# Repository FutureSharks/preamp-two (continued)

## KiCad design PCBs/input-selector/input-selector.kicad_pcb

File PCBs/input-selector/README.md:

# Input Selector

* 6x inputs
* Mute for output
* SPI controlled using a MCP23S17
* Latching relays for low current draw
* Compatible with 5V and 3V relays
* Uses high quality Panasonic relays
* Stackable with [RCA panel](../rca-panel) and [MDAC attenuator](../mdac-attenuator)

## Photos

##  Code

Python module is here: [code/modules/input_selector.py](../../code/modules/input_selector.py)

## Schematic

## Layout

## BoM

| Reference                                 |  Quantity |  Value    |  Footprint / Notes |
|-------------------------------------------|-----------|-----------|-----------------|
| C2, C3, C4                                | 3         | 100nF | 1206 |
| C1_SMD                                    | 1         | 100uF | Radial 10/5mm or SMD, 10V or higher |
| IN1-6, MUTE_IN1, MUTE_OUT1, SELECTOR_OUT1 | 9         | 1x3 | Molex KK 254, Multicomp MC34 or any 0.1" socket header |
| J1                                        | 1         | 1x6 | Molex KK 254, Multicomp MC34 or any 0.1" socket header |
| EXTRA_IO1, PWR1                           | 2         | 1x2 | Molex KK 254, Multicomp MC34 or any 0.1" socket header |
| K1-K6                                     | 6         | G6JU-2P-Y-DC3 | 3V latching coil. e.g. Omron G6J, Panasonic AGN or Tyco IM narrow |
| MUTE1                                     | 1         | G6J-2P-Y-DC3 | 3V non-latching coil. e.g. Omron G6J, Panasonic AGN or Tyco IM narrow |
| R1-9                                      | 12        | 47R | 1206 |
| RLED1                                     | 1         | 1K   | 1206 |
| LED1                                      | 1         | - | 1206 |
| U1, U3                                    | 2         | ULN2003V12DR | SOIC-16 |
| U2                                        | 1         | MCP23S17-E/SO | SOIC 28 wide |

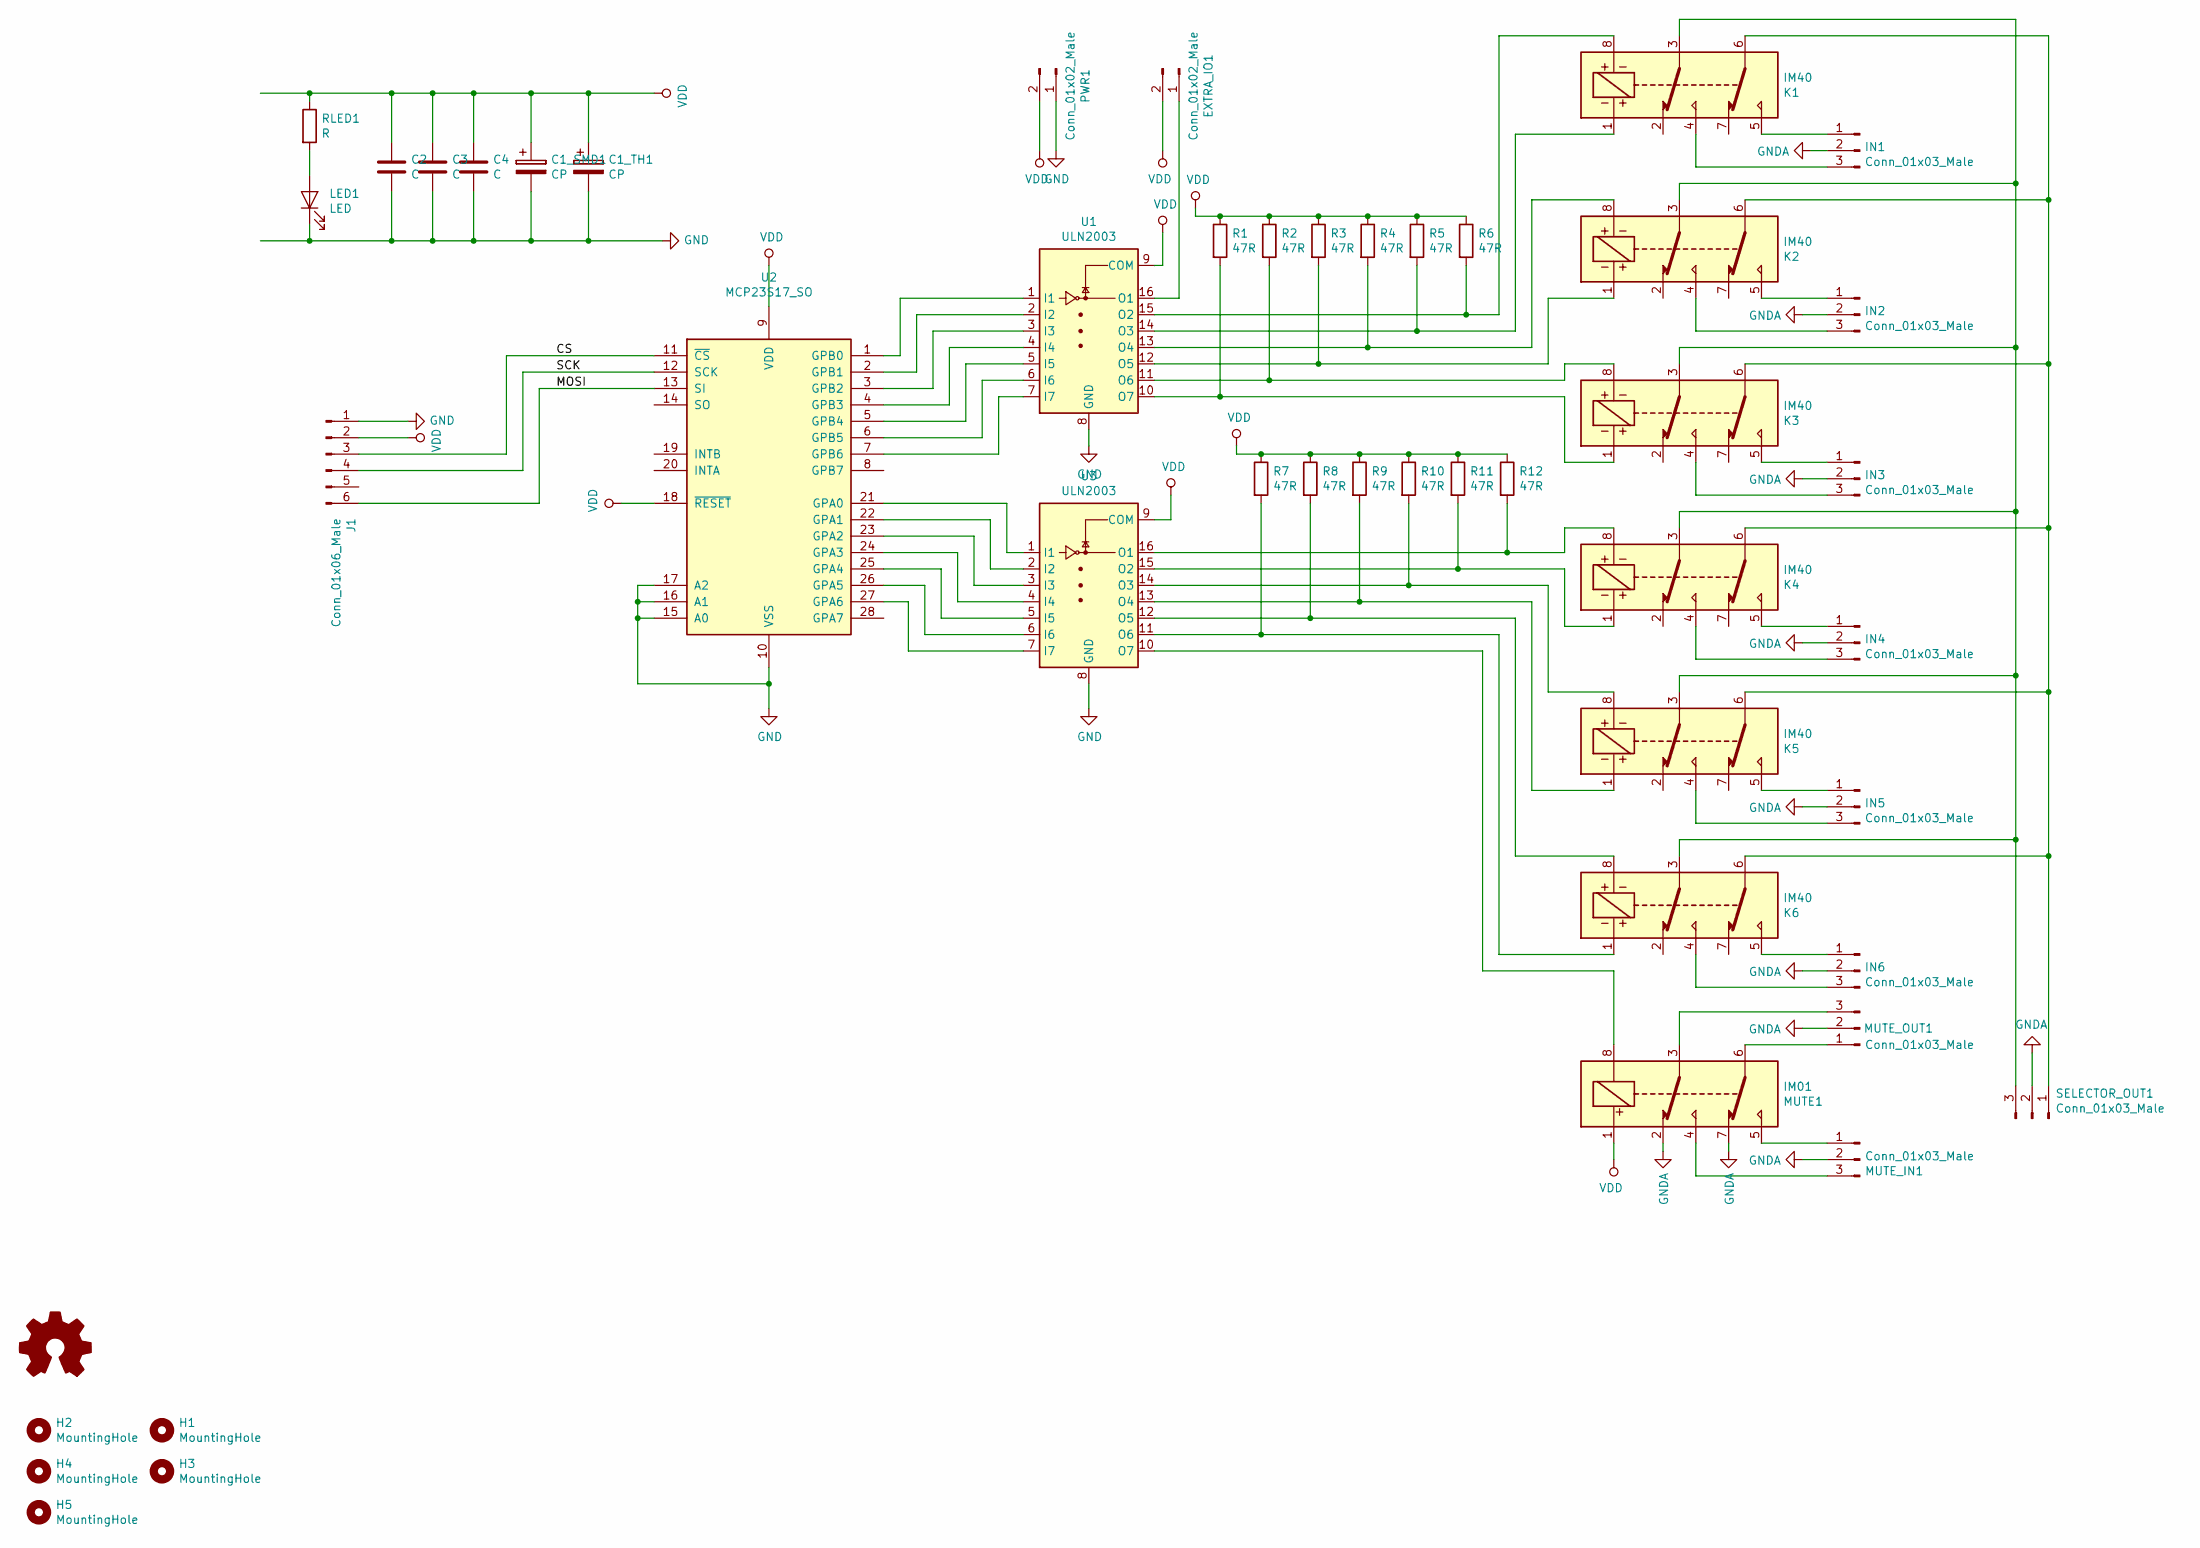
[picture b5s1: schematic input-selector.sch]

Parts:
C1_SMD1: CP; CP_Elec_10x7.9
C1_TH1: CP; CP_Radial_D10.0mm_P5.00mm
C2, C3, C4: C; C_1206_3216Metric_Pad1.42x1.75mm_HandSolder
EXTRA_IO1: Conn_01x02_Male; Molex_KK-254_AE-6410-02A_1x02_P2.54mm_Vertical
H1, H2, H3, H4, H5: MountingHole; MountingHole_3.2mm_M3_DIN965
IN1, IN2, IN3, IN4, IN5, IN6: Conn_01x03_Male; Molex_KK-254_AE-6410-03A_1x03_P2.54mm_Vertical
J1: Conn_01x06_Male; Molex_KK-254_AE-6410-06A_1x06_P2.54mm_Vertical
K1, K2, K3, K4, K5, K6: IM40; g6j-2p-y
LED1: LED; LED_1206_3216Metric
MUTE1: IM01; g6j-2p-y
MUTE_IN1: Conn_01x03_Male; Molex_KK-254_AE-6410-03A_1x03_P2.54mm_Vertical
MUTE_OUT1: Conn_01x03_Male; Molex_KK-254_AE-6410-03A_1x03_P2.54mm_Vertical
PWR1: Conn_01x02_Male; Molex_KK-254_AE-6410-02A_1x02_P2.54mm_Vertical
R1, R2, R3, R4, R5, R6, R7, R8, R9, R10, R11, R12: 47R; R_1206_3216Metric_Pad1.42x1.75mm_HandSolder
RLED1: R; R_1206_3216Metric_Pad1.42x1.75mm_HandSolder
SELECTOR_OUT1: Conn_01x03_Male; Molex_KK-254_AE-6410-03A_1x03_P2.54mm_Vertical
U1, U3: ULN2003; SOIC-16_3.9x9.9mm_P1.27mm
U2: MCP23S17_SO; SOIC-28W_7.5x17.9mm_P1.27mm

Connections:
/CS: J1.3, U2.11 (~CS~)
/MOSI: J1.6, U2.13 (SI)
/SCK: J1.4, U2.12 (SCK)
GND: C1_SMD1.2, C1_TH1.2, C2.2, C3.2, C4.2, J1.1, LED1.1 (K), PWR1.1, U1.8 (GND), U2.10 (VSS), U2.15 (A0), U2.16 (A1), U2.17 (A2), U3.8 (GND)
GNDA: IN1.2, IN2.2, IN3.2, IN4.2, IN5.2, IN6.2, MUTE1.2, MUTE1.7, MUTE_IN1.2, MUTE_OUT1.2, SELECTOR_OUT1.2
unnamed: EXTRA_IO1.1, U1.16 (O1)
unnamed: IN1.1, K1.5
unnamed: IN1.3, K1.4
unnamed: IN2.1, K2.5
unnamed: IN2.3, K2.4
unnamed: IN3.1, K3.5
unnamed: IN3.3, K3.4
unnamed: IN4.1, K4.5
unnamed: IN4.3, K4.4
unnamed: IN5.1, K5.5
unnamed: IN5.3, K5.4
unnamed: IN6.1, K6.5
unnamed: IN6.3, K6.4
unnamed: K1.1, R5.2, U1.14 (O3)
unnamed: K1.3, K2.3, K3.3, K4.3, K5.3, K6.3, SELECTOR_OUT1.3
unnamed: K1.6, K2.6, K3.6, K4.6, K5.6, K6.6, SELECTOR_OUT1.1
unnamed: K1.8, R6.2, U1.15 (O2)
unnamed: K2.1, R3.2, U1.12 (O5)
unnamed: K2.8, R4.2, U1.13 (O4)
unnamed: K3.1, R1.2, U1.10 (O7)
unnamed: K3.8, R2.2, U1.11 (O6)
unnamed: K4.1, R11.2, U3.15 (O2)
unnamed: K4.8, R12.2, U3.16 (O1)
unnamed: K5.1, R9.2, U3.13 (O4)
unnamed: K5.8, R10.2, U3.14 (O3)
unnamed: K6.1, R7.2, U3.11 (O6)
unnamed: K6.8, R8.2, U3.12 (O5)
unnamed: LED1.2 (A), RLED1.2
unnamed: MUTE1.3, MUTE_OUT1.3
unnamed: MUTE1.4, MUTE_IN1.3
unnamed: MUTE1.5, MUTE_IN1.1
unnamed: MUTE1.6, MUTE_OUT1.1
unnamed: MUTE1.8, U3.10 (O7)
unnamed: U1.1 (I1), U2.1 (GPB0)
unnamed: U1.2 (I2), U2.2 (GPB1)
unnamed: U1.3 (I3), U2.3 (GPB2)
unnamed: U1.4 (I4), U2.4 (GPB3)
unnamed: U1.5 (I5), U2.5 (GPB4)
unnamed: U1.6 (I6), U2.6 (GPB5)
unnamed: U1.7 (I7), U2.7 (GPB6)
unnamed: U2.21 (GPA0), U3.1 (I1)
unnamed: U2.22 (GPA1), U3.2 (I2)
unnamed: U2.23 (GPA2), U3.3 (I3)
unnamed: U2.24 (GPA3), U3.4 (I4)
unnamed: U2.25 (GPA4), U3.5 (I5)
unnamed: U2.26 (GPA5), U3.6 (I6)
unnamed: U2.27 (GPA6), U3.7 (I7)
VDD: C1_SMD1.1, C1_TH1.1, C2.1, C3.1, C4.1, EXTRA_IO1.2, J1.2, MUTE1.1, PWR1.2, R1.1, R2.1, R3.1, R4.1, R5.1, R6.1, R7.1, R8.1, R9.1, R10.1, R11.1, R12.1, RLED1.1, U1.9 (COM), U2.9 (VDD), U2.18 (~RESET~), U3.9 (COM)

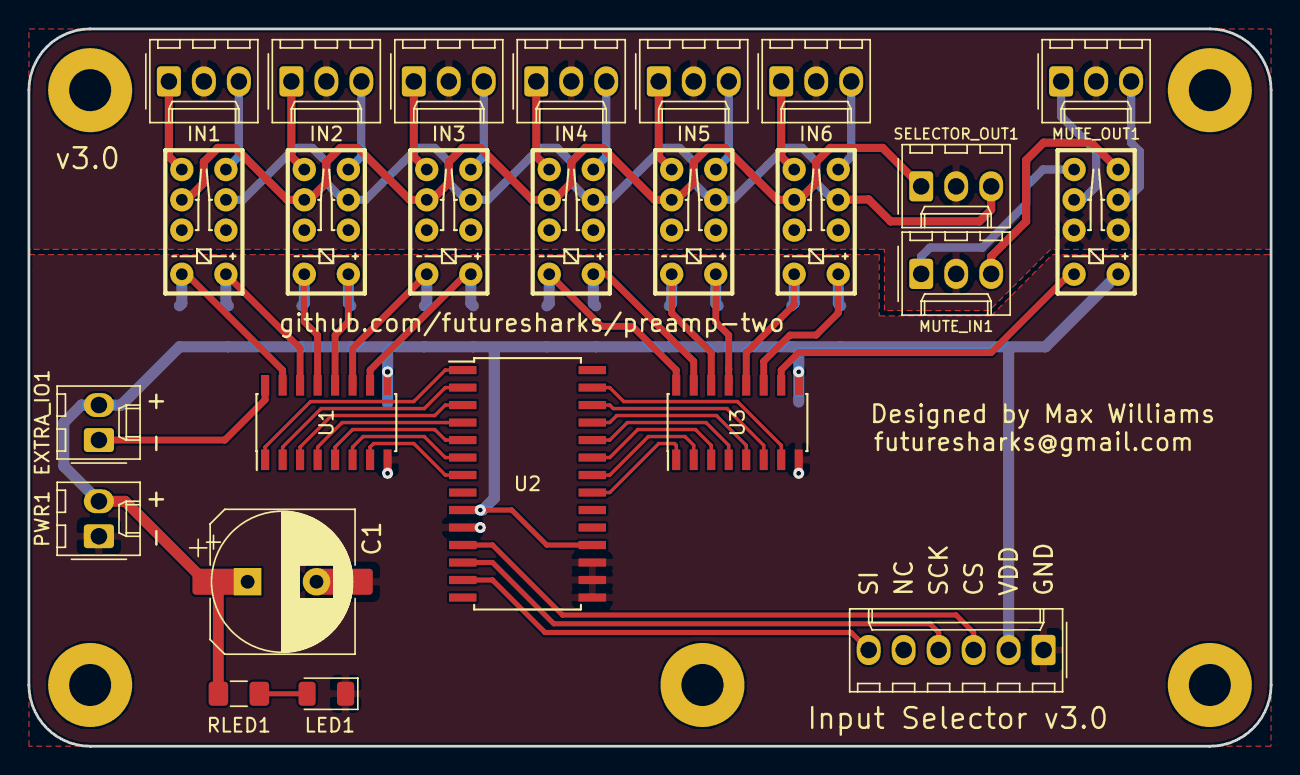
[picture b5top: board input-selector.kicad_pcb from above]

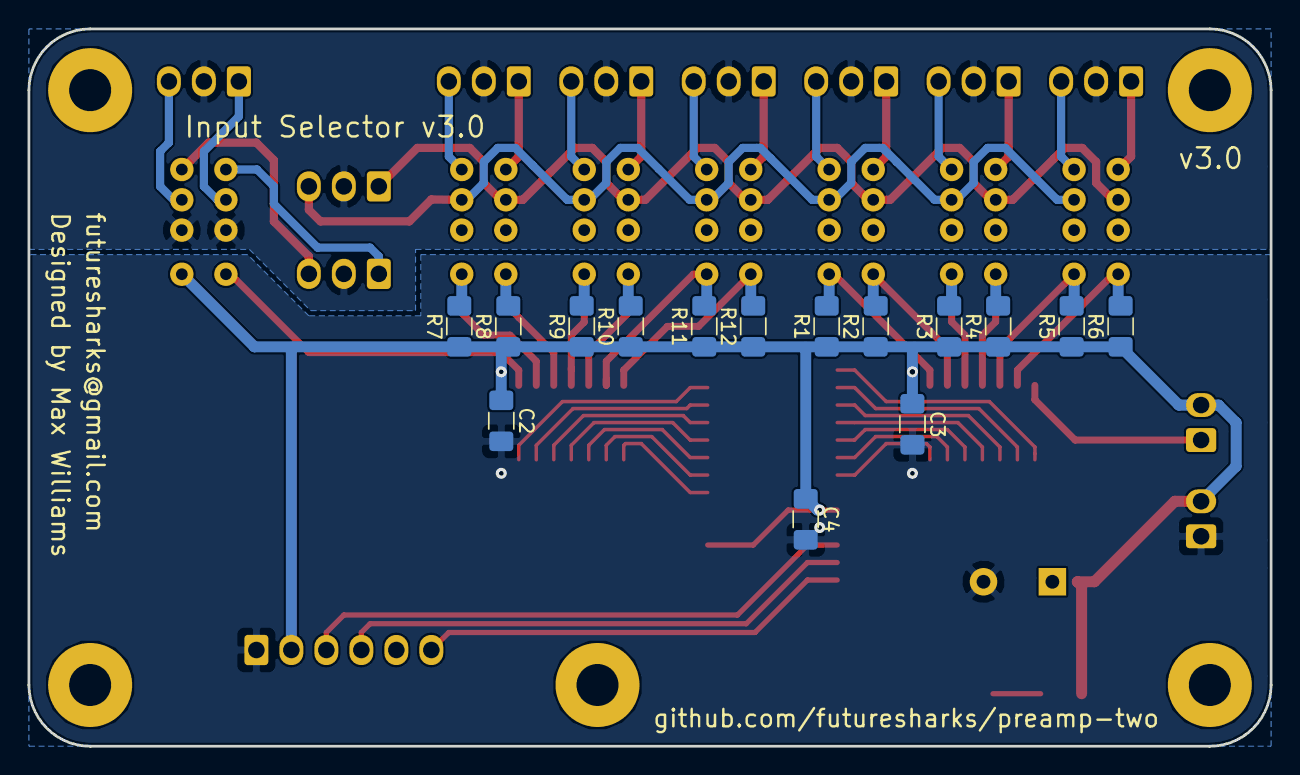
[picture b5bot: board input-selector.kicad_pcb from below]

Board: 2 copper layers, 90.2 x 52.1 mm, 46 parts (15 on the bottom side), 53 nets.

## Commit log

2016-11-29 Adding BoMs
2018-01-30 Adding gain detail
    misc updates
    Revert "misc updates"
    This reverts commit e2f340ec60ba01b13036b8827b0604f6b8269c83.
2018-12-13 adding more test code Merge remote-tracking branch 'origin/master'
    updates to test code
    measuring time
2018-12-13 Moving code to new dir
2018-12-13 Moving test code to new dir
2018-12-13 adding new circuit python modules for each component
2018-12-13 finished circuitpython test code for input selector
2018-12-16 misc fixes for input selector
2018-12-23 adding mdac tester in python
2018-12-28 reorganising PCBs and updating todo
2018-12-29 adding kicad rcs-panel
2018-12-29 update encoder panel
2019-01-01 updating 3 PCBs to kicad
2019-01-03 small input selector update
2019-01-03 Add new text
2019-01-03 Misc updates to 3 PCBs
2019-01-04 updating mcu-board and input selector
2019-01-05 Fixing input selector panasonic relay footprint
2019-01-05 update mcu-board
2019-01-05 Updating all schematics to kicad (#2)
    * adding kicad rcs-panel
    * update encoder panel
    * updating 3 PCBs to kicad
    * small input selector update
    * Add new text
    * Misc updates to 3 PCBs
2019-01-05 Switching relay type to Omron G6J relays
    Since I can't find a source for the others
2019-01-05 Switching relay type to Omron G6J relays (#3)
    Since I can't find a source for the others
2019-01-05 adding BoMs, images and small design updates
2019-01-05 adding BoMs, images and small design updates (#4)
2019-01-06 Updating docs, images etc
2019-01-06 Removing old images
2019-01-06 updating readme and todo
2019-01-08 adding images
2019-01-11 Updating docs, images etc (#5)
    * Updating docs, images etc
2019-01-13 readme updates
2019-01-18 adding digital and analog PSUs
2019-01-22 adding digital and analog PSUs (#6)
2019-01-26 updating PCB after creating new library for newer 805 RCAs
2019-01-26 fix for mounting holes
2019-01-26 New RCA board (#7)
    * updating PCB after creating new library for newer 805 RCAs
    * fix for mounting holes
2019-01-26 Updating mcu-board PCB
2019-01-26 renaming some nets
2019-01-27 starting to fix silkscreen
2019-01-28 readme update
2019-01-28 change pad/mask clearance
2019-01-29 misc updates
2019-01-29 Update RCA panel images
2019-01-29 Addinng PCB for MCU board (#8)
    * Updating mcu-board PCB
    * renaming some nets
    * starting to fix silkscreen
    * change pad/mask clearance
    * misc updates
    * adding images
2019-02-01 misc fixes
2019-02-01 finishing
2019-02-01 tidying up footprints
2019-02-01 removing old libraries
2019-02-01 adding oshpark page break
2019-02-01 updating encoder panel
2019-02-01 renaming symbol to correct name
2019-02-02 Updating encoder panel PCBs (#9)
    * updating encoder panel
    * misc fixes
    * adding oshpark page break
    * renaming symbol to correct name
    * removing old libraries
    * tidying up footprints
2019-03-06 Adding missing BoMs
2019-03-09 adding prototype images
2019-03-09 moving some files
2019-03-17 adding more prototype photos
2019-03-17 updating todo and some code
2019-03-24 code updates for testing
2019-03-24 Misc code fixes, update todo, some readme, (#10)
    * misc fixes
    * code updates for testing
2019-03-27 Updating mcu-board to not use pin 5
2019-03-27 Updating mcu-board to not use pin 5 (#12)
2019-03-29 fixes after testing
2019-03-29 Finishing some code functionality and updating readme
2019-04-02 Finishing some code functionality and updating readme (#11)
    * Finishing some code functionality and updating readme
    * fixes after testing
    * misc updates
    * updates
    * misc updates
    * misc updates
2019-04-11 adding new photos
2019-04-11 adding new photos (#13)
2019-04-12 Adding OSH park link
2019-04-30 getting better
2019-04-30 some working code now
2019-04-30 remove line
2019-04-30 updating images
2019-04-30 MISC
2019-04-30 Adding more images and updating code with a working version (#14)
    * misc updates
    * getting better
    * some working code now
    * updating images
    * remove line
    * MISC
2019-05-01 adding a gif
2019-06-10 add enclosure info
2019-06-10 update bom to m4
2019-06-10 fix MDAC level bug
2019-06-10 switching arrangement of modules
2019-06-10 removing old arduino sketch
2019-06-10 misc changes
2019-06-10 adding ring fading after timeout
2019-06-16 moving dirs outside of images dir
2019-06-16 update todo
2019-06-16 more code changes
2019-06-16 updates to images
2019-06-16 typo in image path
2019-06-16 add prototype image
2019-06-16 add encoder_panel back
2019-06-16 fixing offset calculation
2019-06-25 adding a gif
    add enclosure info
    update bom to m4
    fix MDAC level bug
    switching arrangement of modules
    removing old arduino sketch
    misc changes
2019-07-20 updating 3d files
2019-07-27 switch to use object inheritance for the encoder panel
    to reduce duplicated code
2019-07-27 rewrite of colour calculation
2019-08-01 changing input control LED style
2019-08-10 finally colours working nicely
2019-08-10 fix debug mode
2019-08-10 tidy up
2019-08-10 Switch to use object inheritance for the encoder panel modules (#16)
    * switch to use object inheritance for the encoder panel
    to reduce duplicated code
    * rewrite of colour calculation
    * changing input control LED style
    * finally colours working nicely
    * fix debug mode
2019-08-18 General tidy up
2019-08-18 General tidy up (#17)
2019-09-12 Updating bearing bracket and mute delay
2019-09-13 Updating bearing bracket and mute delay (#18)
2021-11-08 Update README.md
    https://forum.kicad.info/t/warning-avoid-all-links-to-kicad-pcb-org-use-kicad-org/31521/
2021-11-08 Update README.md (#20)
    https://forum.kicad.info/t/warning-avoid-all-links-to-kicad-pcb-org-use-kicad-org/31521/
